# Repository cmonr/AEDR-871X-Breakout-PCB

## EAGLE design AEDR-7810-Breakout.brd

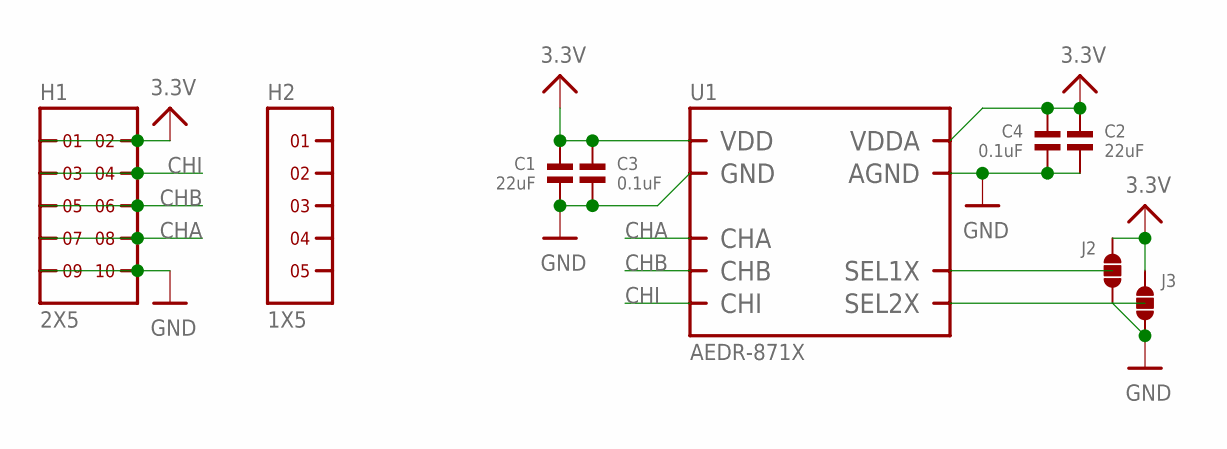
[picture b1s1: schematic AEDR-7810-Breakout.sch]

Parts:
C1, C2: 22uF; 0805
C3, C4: 0.1uF; 0603
H1: 2X5
H2: 1X5
J2, J3: SOLDERJUMPER.3.MED.12; 3.MED.12
U1: AEDR-871X

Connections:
3.3V: C1.1, C2.1, C3.1, C4.1, H1.1, H1.2, J2.1, J3.1, U1.1 (VDDA), U1.8 (VDD)
CHA: H1.7, H1.8, U1.7 (CHA)
CHB: H1.5, H1.6, U1.6 (CHB)
CHI: H1.3, H1.4, U1.5 (CHI)
GND: C1.2, C2.2, C3.2, C4.2, H1.9, H1.10, J2.3, J3.3, U1.2 (AGND), U1.PAD (GND)
unnamed: J2.2, U1.3 (SEL1X)
unnamed: J3.2, U1.4 (SEL2X)

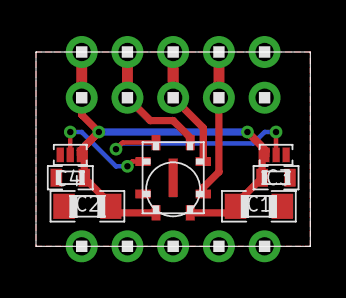
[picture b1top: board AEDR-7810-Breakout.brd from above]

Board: 2 copper layers, 15.2 x 10.8 mm, 9 parts (0 on the bottom side), 7 nets.

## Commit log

2016-01-19 Starting to layout board
2016-01-19 Updated board preview
2016-01-21 Completed initial rev of breakout

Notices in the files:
parts and their libraries:
microbuilder: This work is placed in the public domain, and may be freely used for commercial and non-commercial work with the following conditions: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
